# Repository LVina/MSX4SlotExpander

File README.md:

# MSX4SlotExpander
MSX 4 Slots Expander Cartridge

Simple no buffered 4 slot expander.
Project is based on Ciel expander and PCB layout is intended to be used in the Back Slot.
Next steps:
  1- Test on protoboard.
  2- 3D Case design.
  3- Prototype PCB manufacture.

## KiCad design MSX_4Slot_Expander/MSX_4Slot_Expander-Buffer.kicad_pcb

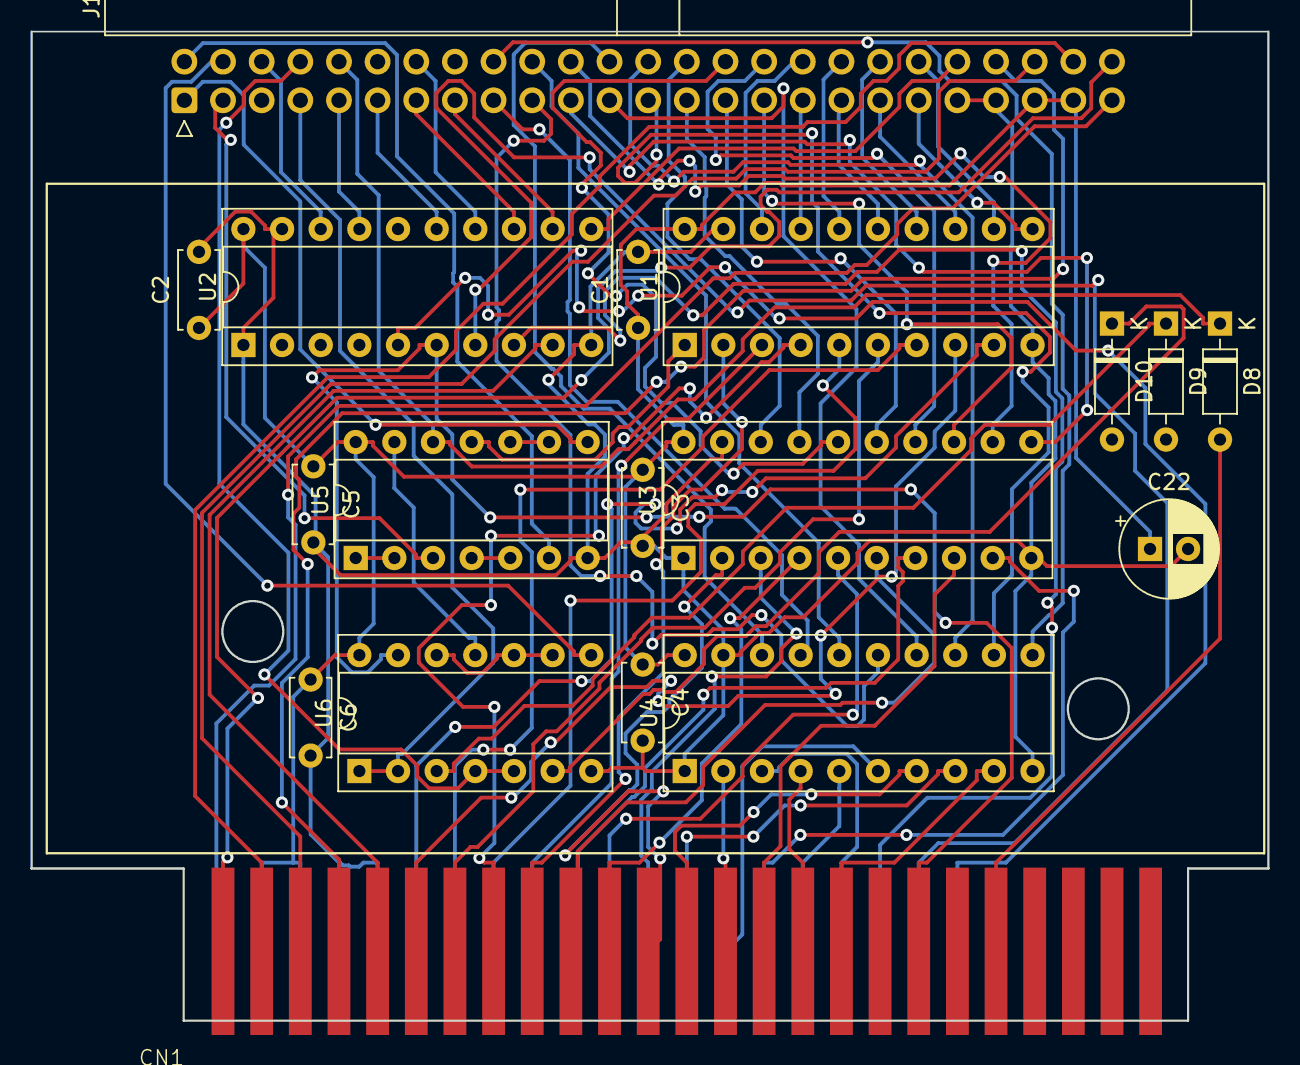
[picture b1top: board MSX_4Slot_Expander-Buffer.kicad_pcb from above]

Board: 2 copper layers, 81.3 x 65.0 mm, 18 parts (0 on the bottom side), 83 nets.

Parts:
C1, C2, C3, C4, C5, C6: 104; C_Disc_D5.0mm_W2.5mm_P5.00mm
C22: 100uF; CP_Radial_D6.3mm_P2.50mm
CN1: MSX_SLOT_CON-msxmakers; MSX_Slot
D8, D9, D10: 1N914; D_DO-35_SOD27_P7.62mm_Horizontal
J1: Conn_02x25_Odd_Even; IDC-Header_2x25_P2.54mm_Horizontal
U1: 74HC245; DIP-20_W7.62mm_Socket
U2, U3, U4: 74HCT541; DIP-20_W7.62mm_Socket
U5: 74LS08; DIP-14_W7.62mm_Socket
U6: 74HCT32; DIP-14_W7.62mm_Socket

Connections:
+5V: C1.1, C2.1, C3.1, C4.1, C5.1, C6.1, C22.1, CN1.45 (+5V1), CN1.47 (+5V2), J1.45, J1.47, U1.20 (VCC), U2.20 (VCC), U3.20 (VCC), U4.20 (VCC), U5.14 (VCC), U6.14 (VCC)
+12V: CN1.48 (+12V), J1.48
-12V: CN1.50 (-12V), J1.50
A0: CN1.28 (A0), U3.2 (A0)
A1: CN1.27 (A1), U3.3 (A1)
A2: CN1.30 (A2), U3.4 (A2)
A3: CN1.29 (A3), U3.5 (A3)
A4: CN1.32 (A4), U3.6 (A4)
A5: CN1.31 (A5), U3.7 (A5)
A6: CN1.22 (A6), U3.8 (A6)
A7: CN1.21 (A7), U3.9 (A7)
A8: CN1.24 (A8), U4.2 (A0)
A9: CN1.17 (A9), U4.3 (A1)
A10: CN1.20 (A10), U4.4 (A2)
A11: CN1.19 (A11), U4.5 (A3)
A12: CN1.23 (A12), U4.6 (A4)
A13: CN1.26 (A13), U4.7 (A5)
A14: CN1.25 (A14), U4.8 (A6)
A15: CN1.18 (A15), U4.9 (A7)
BUSDIR: CN1.10 (~BUSDIR), D8.2 (A)
BXA0: J1.28, U3.18 (Y0)
BXA1: J1.27, U3.17 (Y1)
BXA2: J1.30, U3.16 (Y2)
BXA3: J1.29, U3.15 (Y3)
BXA4: J1.32, U3.14 (Y4)
BXA5: J1.31, U3.13 (Y5)
BXA6: J1.22, U3.12 (Y6)
BXA7: J1.21, U3.11 (Y7)
BXA8: J1.24, U4.18 (Y0)
BXA9: J1.17, U4.17 (Y1)
BXA10: J1.20, U4.16 (Y2)
BXA11: J1.19, U4.15 (Y3)
BXA12: J1.23, U4.14 (Y4)
BXA13: J1.26, U4.13 (Y5)
BXA14: J1.25, U4.12 (Y6)
BXA15: J1.18, U4.11 (Y7)
BXCLK: J1.42, U2.11 (Y7)
BXCS1: J1.1, U5.8
BXCS2: J1.2, U5.6
BXCS12: J1.3, U5.3
BXD0: J1.34, U1.18 (B0)
BXD1: J1.33, U1.17 (B1)
BXD2: J1.36, U1.16 (B2)
BXD3: J1.35, U1.15 (B3)
BXD4: J1.38, U1.14 (B4)
BXD5: J1.37, U1.13 (B5)
BXD6: J1.40, U1.12 (B6)
BXD7: J1.39, U1.11 (B7)
BXDIR: D8.1 (K), J1.10, U5.12
BXINT: J1.8, U6.4, U6.5
BXIORQ: J1.11, U2.15 (Y3)
BXM1: J1.9, U2.17 (Y1)
BXRD: J1.14, U2.14 (Y4)
BXRESET: J1.15, U2.12 (Y6)
BXRFSH: J1.6, U2.18 (Y0)
BXSLTSL: J1.4, U6.8
BXWAIT: J1.7, U6.1, U6.2
BXWR: J1.13, U2.13 (Y5)
CLK: CN1.42 (CLOCK), U2.9 (A7)
CS1: U5.9, U5.10
CS2: U5.4, U5.5
CS12: U5.1, U5.2
D0: CN1.34 (D0), U1.2 (A0)
D1: CN1.33 (D1), U1.3 (A1)
D2: CN1.36 (D2), U1.4 (A2)
D3: CN1.35 (D3), U1.5 (A3)
D4: CN1.38 (D4), U1.6 (A4)
D5: CN1.37 (D5), U1.7 (A5)
D6: CN1.40 (D6), U1.8 (A6)
D7: CN1.39 (D7), U1.9 (A7)
Earth: C1.2, C2.2, C3.2, C4.2, C5.2, C6.2, C22.2, CN1.41 (GND1), CN1.43 (GND2), J1.41, J1.43, U1.10 (GND), U1.19 (CE), U2.1 (G1), U2.10 (GND), U2.19 (G2), U3.1 (G1), U3.10 (GND), U3.19 (G2), U4.1 (G1), U4.10 (GND), U4.19 (G2), U5.7 (GND), U6.7 (GND)
IORQ: CN1.11 (~IORQ), U2.5 (A3)
unnamed: D9.1 (K), U6.3
unnamed: D10.1 (K), U6.6
unnamed: U1.1 (A->B), U5.11
unnamed: U5.13, U6.11
RD: CN1.14 (~RD), U2.6 (A4), U6.13
RESET: CN1.15 (~RESET), U2.8 (A6)
SLTSL: U6.9, U6.10, U6.12
SNDIN: CN1.49 (SNDIN), J1.49
SW1: CN1.44 (SW1), J1.44
SW2: CN1.46 (SW2), J1.46
WR: CN1.13 (~WR), U2.7 (A5)

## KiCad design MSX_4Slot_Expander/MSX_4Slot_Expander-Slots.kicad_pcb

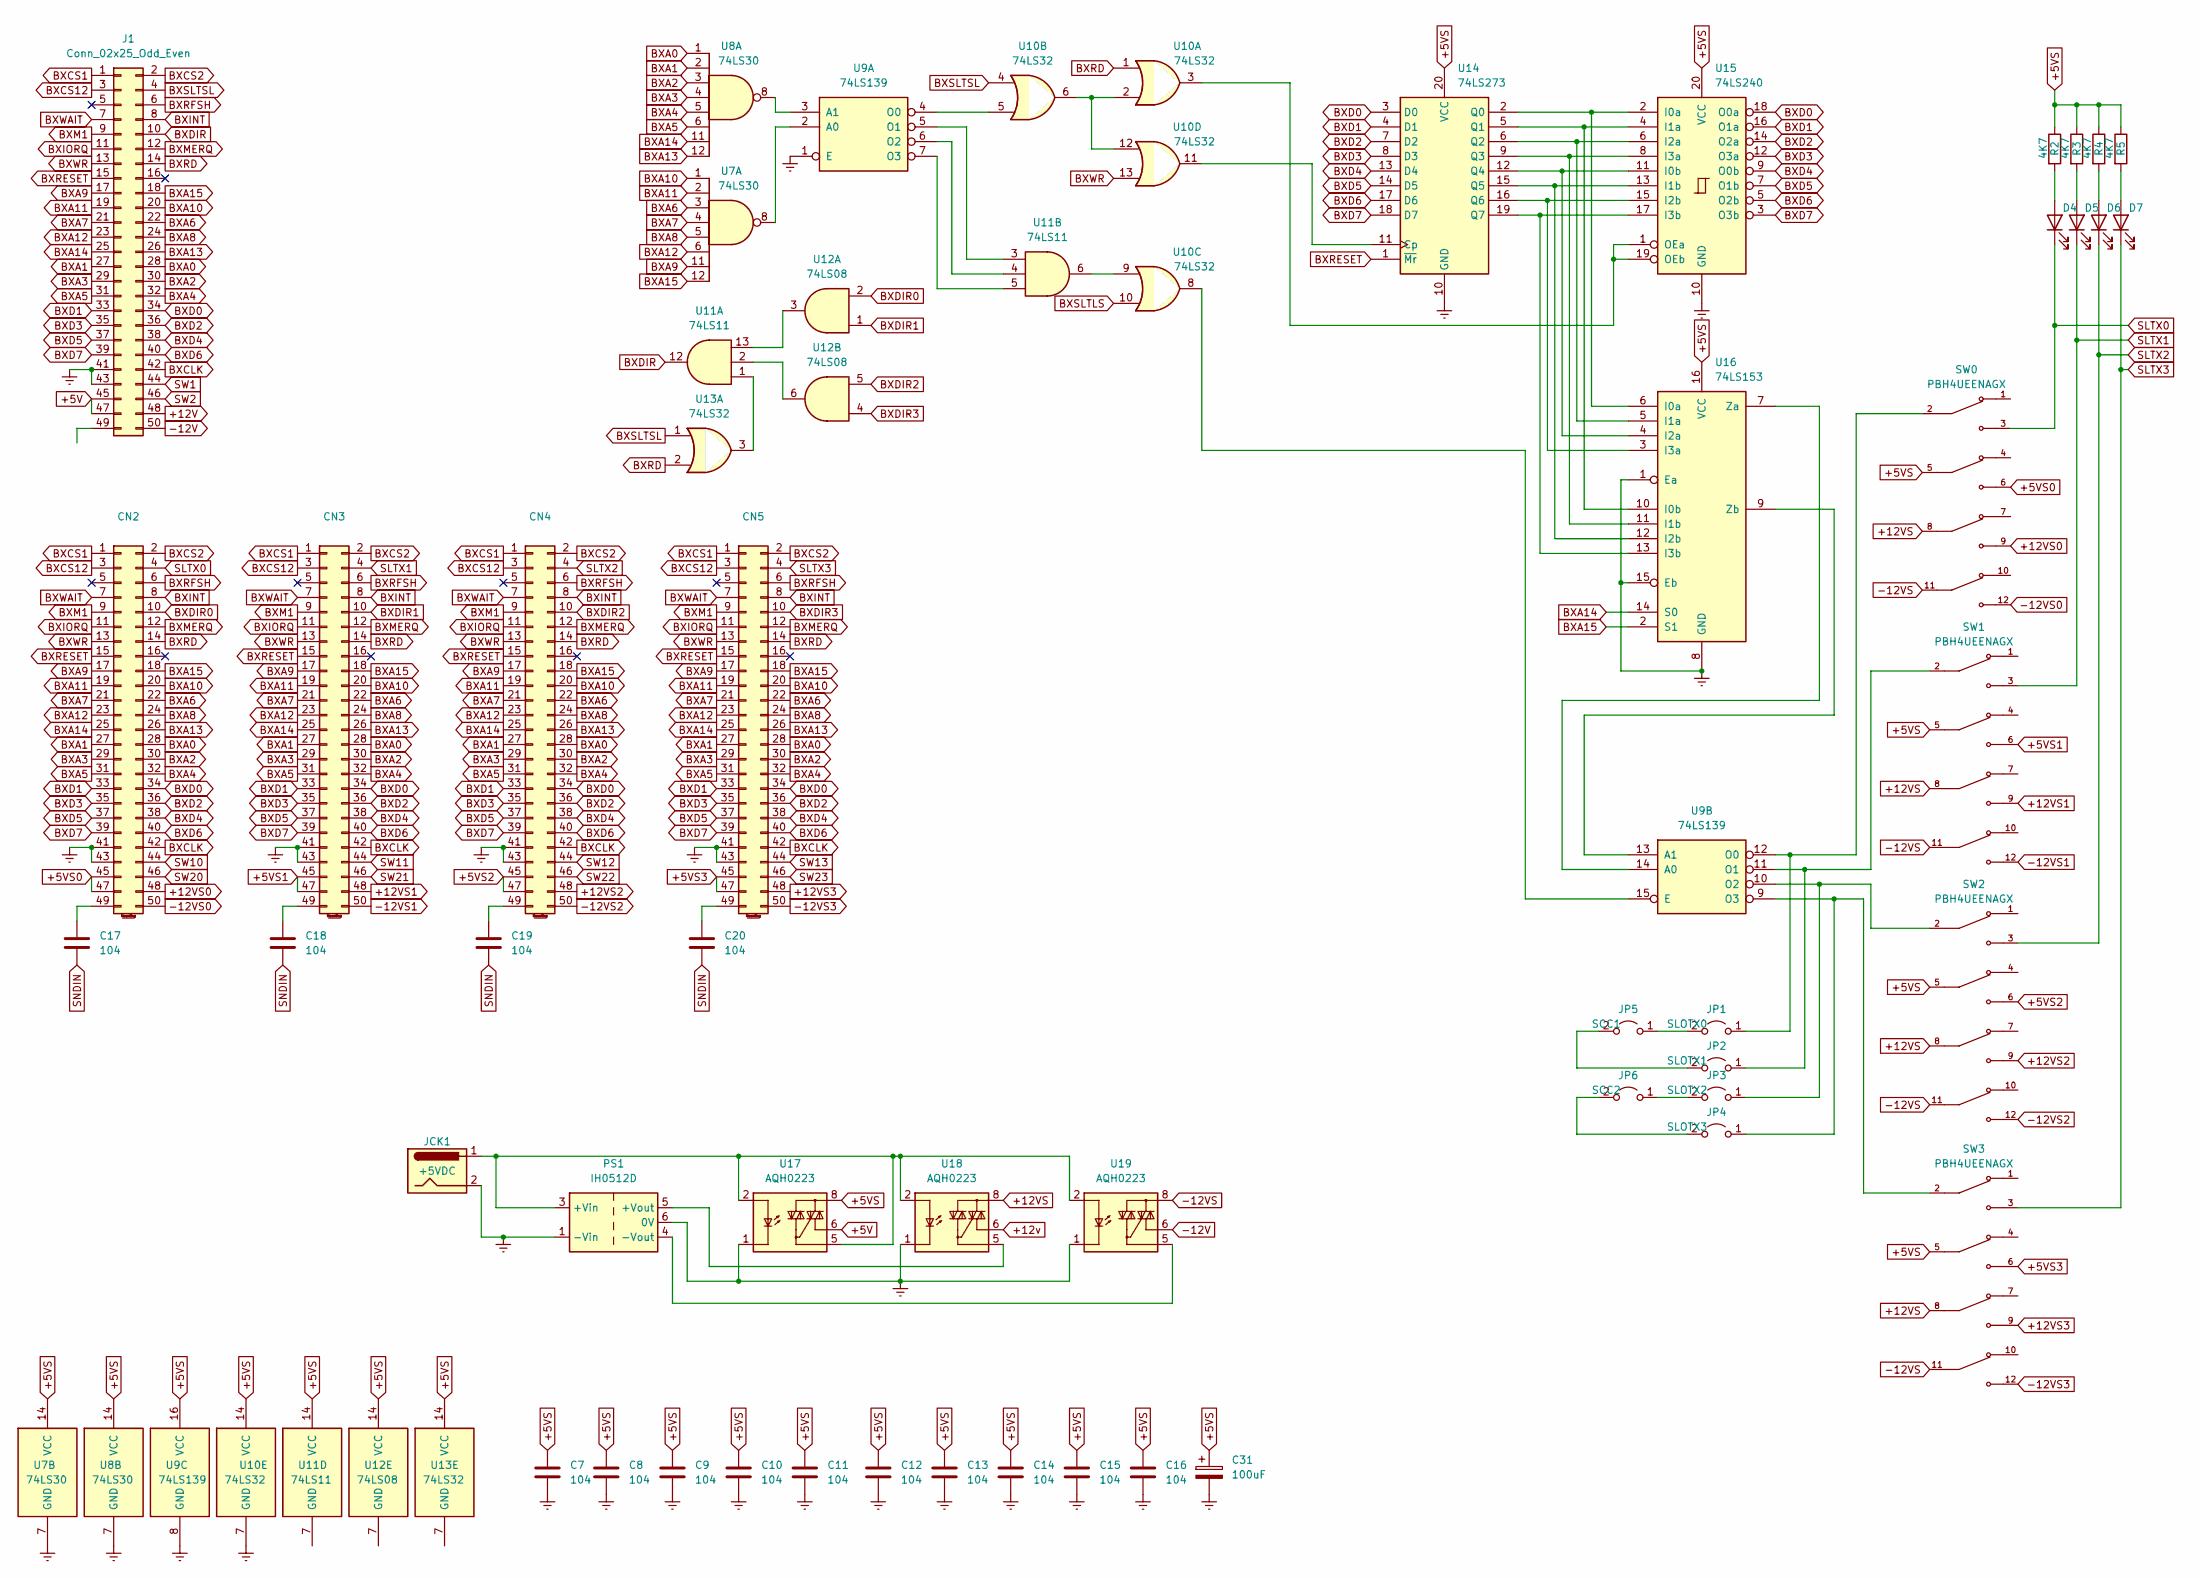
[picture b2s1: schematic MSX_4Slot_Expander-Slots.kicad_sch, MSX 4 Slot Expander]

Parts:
C7, C8, C9, C10, C11, C12, C13, C14, C15, C16, C17, C18, C19, C20: 104; C_Disc_D5.0mm_W2.5mm_P5.00mm
C31: 100uF; CP_Radial_D6.3mm_P2.50mm
CN2, CN3, CN4, CN5: Conn_02x25_Odd_Even_MountingPin; Connector EDGE 2x25 2.54mm
D4, D5, D6, D7: LED; LED_D1.8mm_W3.3mm_H2.4mm
J1: Conn_02x25_Odd_Even; IDC-Header_2x25_P2.54mm_Horizontal
JCK1: +5VDC; BarrelJack_CUI_PJ-063AH_Horizontal
JP1: SLOTX0; PinHeader_1x02_P2.54mm_Vertical
JP2: SLOTX1; PinHeader_1x02_P2.54mm_Vertical
JP3: SLOTX2; PinHeader_1x02_P2.54mm_Vertical
JP4: SLOTX3; PinHeader_1x02_P2.54mm_Vertical
JP5: SCC1; PinHeader_1x02_P2.54mm_Vertical
JP6: SCC2; PinHeader_1x02_P2.54mm_Vertical
PS1: IH0512D; Converter_DCDC_XP_POWER-IHxxxxD_THT
R2, R3, R4, R5: 4K7; R_Axial_DIN0207_L6.3mm_D2.5mm_P7.62mm_Horizontal
SW0, SW1, SW2, SW3: PBH4UEENAGX; SW_PBH4UEENAGX; PARTREV E
U7, U8: 74LS30; DIP-14_W7.62mm_Socket
U9: 74LS139; DIP-16_W7.62mm_Socket
U10, U13: 74LS32; DIP-14_W7.62mm_Socket
U11: 74LS11; DIP-14_W7.62mm_Socket
U12: 74LS08; DIP-14_W7.62mm_Socket
U14: 74LS273; DIP-20_W7.62mm_Socket
U15: 74LS240; DIP-20_W7.62mm_Socket
U16: 74LS153; DIP-16_W7.62mm_Socket
U17, U18, U19: AQH0223; DIP-8-N7_W7.62mm

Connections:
+5V: J1.45, J1.47, U17.6
+5VS: C7.1, C8.1, C9.1, C10.1, C11.1, C12.1, C13.1, C14.1, C15.1, C16.1, C31.1, R2.1, R3.1, R4.1, R5.1, SW0.5, SW1.5, SW2.5, SW3.5, U7.14 (VCC), U8.14 (VCC), U9.16 (VCC), U10.14 (VCC), U11.14 (VCC), U12.14 (VCC), U13.14 (VCC), U14.20 (VCC), U15.20 (VCC), U16.16 (VCC), U17.8
+5VS0: CN2.45, CN2.47, SW0.6
+5VS1: CN3.45, CN3.47, SW1.6
+5VS2: CN4.45, CN4.47, SW2.6
+5VS3: CN5.45, CN5.47, SW3.6
+12V: J1.48
+12VS: SW0.8, SW1.8, SW2.8, SW3.8, U18.8
+12VS0: CN2.48, SW0.9
+12VS1: CN3.48, SW1.9
+12VS2: CN4.48, SW2.9
+12VS3: CN5.48, SW3.9
+12v: U18.6
-12V: J1.50, U19.6
-12VS: SW0.11, SW1.11, SW2.11, SW3.11, U19.8
-12VS0: CN2.50, SW0.12
-12VS1: CN3.50, SW1.12
-12VS2: CN4.50, SW2.12
-12VS3: CN5.50, SW3.12
BXA0: CN2.28, CN3.28, CN4.28, CN5.28, J1.28, U8.1
BXA1: CN2.27, CN3.27, CN4.27, CN5.27, J1.27, U8.2
BXA2: CN2.30, CN3.30, CN4.30, CN5.30, J1.30, U8.3
BXA3: CN2.29, CN3.29, CN4.29, CN5.29, J1.29, U8.4
BXA4: CN2.32, CN3.32, CN4.32, CN5.32, J1.32, U8.5
BXA5: CN2.31, CN3.31, CN4.31, CN5.31, J1.31, U8.6
BXA6: CN2.22, CN3.22, CN4.22, CN5.22, J1.22, U7.3
BXA7: CN2.21, CN3.21, CN4.21, CN5.21, J1.21, U7.4
BXA8: CN2.24, CN3.24, CN4.24, CN5.24, J1.24, U7.5
BXA9: CN2.17, CN3.17, CN4.17, CN5.17, J1.17, U7.11
BXA10: CN2.20, CN3.20, CN4.20, CN5.20, J1.20, U7.1
BXA11: CN2.19, CN3.19, CN4.19, CN5.19, J1.19, U7.2
BXA12: CN2.23, CN3.23, CN4.23, CN5.23, J1.23, U7.6
BXA13: CN2.26, CN3.26, CN4.26, CN5.26, J1.26, U8.12
BXA14: CN2.25, CN3.25, CN4.25, CN5.25, J1.25, U8.11, U16.14 (S0)
BXA15: CN2.18, CN3.18, CN4.18, CN5.18, J1.18, U7.12, U16.2 (S1)
BXCLK: CN2.42, CN3.42, CN4.42, CN5.42, J1.42
BXCS1: CN2.1, CN3.1, CN4.1, CN5.1, J1.1
BXCS2: CN2.2, CN3.2, CN4.2, CN5.2, J1.2
BXCS12: CN2.3, CN3.3, CN4.3, CN5.3, J1.3
BXD0: CN2.34, CN3.34, CN4.34, CN5.34, J1.34, U14.3 (D0), U15.18 (O0a)
BXD1: CN2.33, CN3.33, CN4.33, CN5.33, J1.33, U14.4 (D1), U15.16 (O1a)
BXD2: CN2.36, CN3.36, CN4.36, CN5.36, J1.36, U14.7 (D2), U15.14 (O2a)
BXD3: CN2.35, CN3.35, CN4.35, CN5.35, J1.35, U14.8 (D3), U15.12 (O3a)
BXD4: CN2.38, CN3.38, CN4.38, CN5.38, J1.38, U14.13 (D4), U15.9 (O0b)
BXD5: CN2.37, CN3.37, CN4.37, CN5.37, J1.37, U14.14 (D5), U15.7 (O1b)
BXD6: CN2.40, CN3.40, CN4.40, CN5.40, J1.40, U14.17 (D6), U15.5 (O2b)
BXD7: CN2.39, CN3.39, CN4.39, CN5.39, J1.39, U14.18 (D7), U15.3 (O3b)
BXDIR: J1.10, U11.12
BXDIR0: CN2.10, U12.2
BXDIR1: CN3.10, U12.1
BXDIR2: CN4.10, U12.5
BXDIR3: CN5.10, U12.4
BXINT: CN2.8, CN3.8, CN4.8, CN5.8, J1.8
BXIORQ: CN2.11, CN3.11, CN4.11, CN5.11, J1.11
BXM1: CN2.9, CN3.9, CN4.9, CN5.9, J1.9
BXMERQ: CN2.12, CN3.12, CN4.12, CN5.12, J1.12
BXRD: CN2.14, CN3.14, CN4.14, CN5.14, J1.14, U10.1, U13.2
BXRESET: CN2.15, CN3.15, CN4.15, CN5.15, J1.15, U14.1 (~Mr)
BXRFSH: CN2.6, CN3.6, CN4.6, CN5.6, J1.6
BXSLTLS: U10.10
BXSLTSL: J1.4, U10.4, U13.1
BXWAIT: CN2.7, CN3.7, CN4.7, CN5.7, J1.7
BXWR: CN2.13, CN3.13, CN4.13, CN5.13, J1.13, U10.13
Earth: C7.2, C8.2, C9.2, C10.2, C11.2, C12.2, C13.2, C14.2, C15.2, C16.2, C31.2, CN2.41, CN2.43, CN3.41, CN3.43, CN4.41, CN4.43, CN5.41, CN5.43, J1.41, J1.43, JCK1.2, PS1.1 (-Vin), PS1.6 (0V), U7.7 (GND), U8.7 (GND), U9.1 (E), U9.8 (GND), U10.7 (GND), U14.10 (GND), U15.10 (GND), U16.1 (Ea), U16.8 (GND), U16.15 (Eb), U17.1, U17.3, U17.4, U18.1, U18.3, U18.4, U19.1, U19.3, U19.4
unnamed: C17.1, CN2.49
unnamed: C18.1, CN3.49
unnamed: C19.1, CN4.49
unnamed: C20.1, CN5.49
unnamed: D4.2 (A), R2.2
unnamed: D5.2 (A), R3.2
unnamed: D6.2 (A), R4.2
unnamed: D7.2 (A), R5.2
unnamed: JP1.1 (A), SW0.2, U9.12 (O0)
unnamed: JP1.2 (B), JP5.1 (A)
unnamed: JP2.1 (A), SW1.2, U9.11 (O1)
unnamed: JP2.2 (B), JP5.2 (B)
unnamed: JP3.1 (A), SW2.2, U9.10 (O2)
unnamed: JP3.2 (B), JP6.1 (A)
unnamed: JP4.1 (A), SW3.2, U9.9 (O3)
unnamed: JP4.2 (B), JP6.2 (B)
unnamed: JCK1.1, PS1.3 (+Vin), U17.2, U17.5, U18.2, U19.2
unnamed: PS1.5 (+Vout), U18.5
unnamed: PS1.4 (-Vout), U19.5
unnamed: U7.8, U9.2 (A0)
unnamed: U8.8, U9.3 (A1)
unnamed: U9.4 (O0), U10.5
unnamed: U9.5 (O1), U11.3
unnamed: U9.6 (O2), U11.4
unnamed: U9.7 (O3), U11.5
unnamed: U9.15 (E), U10.8
unnamed: U10.9, U11.6
unnamed: U10.2, U10.6, U10.12
unnamed: U11.1, U13.3
unnamed: U11.2, U12.6
unnamed: U11.13, U12.3
unnamed: U10.11, U14.11 (Cp)
unnamed: U14.2 (Q0), U15.2 (I0a), U16.6 (I0a)
unnamed: U14.5 (Q1), U15.4 (I1a), U16.10 (I0b)
unnamed: U14.6 (Q2), U15.6 (I2a), U16.5 (I1a)
unnamed: U14.9 (Q3), U15.8 (I3a), U16.11 (I1b)
unnamed: U14.12 (Q4), U15.11 (I0b), U16.4 (I2a)
unnamed: U14.15 (Q5), U15.13 (I1b), U16.12 (I2b)
unnamed: U14.16 (Q6), U15.15 (I2b), U16.3 (I3a)
unnamed: U14.19 (Q7), U15.17 (I3b), U16.13 (I3b)
unnamed: U10.3, U15.1 (OEa), U15.19 (OEb)
unnamed: U9.14 (A0), U16.7 (Za)
unnamed: U9.13 (A1), U16.9 (Zb)
SLTX0: CN2.4, D4.1 (K), SW0.3
SLTX1: CN3.4, D5.1 (K), SW1.3
SLTX2: CN4.4, D6.1 (K), SW2.3
SLTX3: CN5.4, D7.1 (K), SW3.3
SNDIN: C17.2, C18.2, C19.2, C20.2
SW1: J1.44
SW2: J1.46
SW10: CN2.44
SW11: CN3.44
SW12: CN4.44
SW13: CN5.44
SW20: CN2.46
SW21: CN3.46
SW22: CN4.46
SW23: CN5.46

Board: 2 copper layers, 53 parts (0 on the bottom side), 109 nets, no tracks yet.

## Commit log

2024-02-11 README.md
2024-02-13 Add files via upload
    Added buffers and external +5v supply
